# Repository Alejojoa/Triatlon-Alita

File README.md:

# Robot Triatlon - "ALITA" - SPACE ANGELS ROBOTICS

### Robot de competición desarrollado en el año 2024 por "Space Angels Robotics", con el objetivo de participar de los Juegos Bonaerenses del correspondiente año en la categoría de "Triatlón Robótico".
Campéon Regional en la categoría de "Triatlón Robótico" en la Universidad de Quilmes el (22 Ago).
Participación en los Juegos Bonaerenses 2024 (28 Oct. - 2 Nov.)

Llevado a cabo por alumnos de 6to año de la Técnica n°5 "2 de Abril" en la carrera de Electrónica.
Alita es un robot diseñado para fines plenamente educativos, contado con múltiples versiones, con el objetivo de superarse a si misma en cada una de sus etapas.

Todo el proyecto ha sido realizado en Vistual Studio Code con la extensión de PlarformIO en lenguaje C++ Orientado a Objetos.
Diseño de PCBs realizado en KiCad 8.0
Diseño de Hardware3D en Fusion 360

Participantes: Guerra Alejo Joaqín
               Lazzatti Lucas
               Regidor Jeremías
               Romano Iván
               Rossi Mamberti Valentina Jenifer

Director Técnico: Prof. Barzola Maximiliano Andrés

 Este robót cuenta con diferentes categorías, de las cuales cada una tendrá su rama individual con su última versión vigente.

 ## despeja_area
 Rama dedicada a la programación final (Alita V3) en la categoría de "Despeja Area" (Autonomo). Su objetivo será el de quitar de la pista una serie de cubos de la forma más rápida y eficiente posible, sin salir de la pista. 

   -.vscode
        Archivos generados por el IDE Visual Studio Code y la extensión de PlatformIO.
        
   -fimware
        Código actual individual de despeja_area.

 ## sprinter
 Rama dedicada a la programación final (Alita V3) en la categoría de "Velocista" (Autonomo). Su objetivo será el de completar una pista en su totalidad de la forma más rápida posible, pudiendo de igual forma incluir obstáculos o no.

   -.vscode
        Archivos generados por el IDE Visual Studio Code y la extensión de PlatformIO.
        
   -fimware
        Código actual individual de sprinter.

 ## sumo
 Rama dedicada a la programación final (Alita V3) en la categoría de "Sumo RC" (Radio Controlado). Su objertivo será el de quitar del tatami al rival, siendo un operario el encargado de manejar el robot. 

   -.vscode
        Archivos generados por el IDE Visual Studio Code y la extensión de PlatformIO.

   -fimware
        Código actual indiviual de sumo.

 ## menu
 Alita, en todas sus versiónes, incluye un menu comandado por pulsadores incluidos en el lateral izquierdo de robot para mayor comodidad del usuario. En esta rama encontrará la programación dedicada al manejo de esta interfaz. 

  -.vscode
       Archivos generados por el IDE Visual Studio Code y la extensión de PlatformIO.

  -fimware
       Programación de la interfaz de menú.

 ## main
 Esta es la rama principal del repositorio. En ella se encontrará la union de todas las ramas en una sola junto al hardware de Alita.

   -.vscode
        Archivos generados por el IDE Vistual Studio Code y la extensión de PlatformIO.

   -fimware
        Unión de las ramas individuales en una sola para mayor comodidad, dandole así a la interfaz del menu.

   -hardware
        PCBs empleadas en el robot, tanto como principales como drivers y multiplexores.

   -hardware 3D
        Diseños 3D de las diferentes versiones de Alita.

 ## stage
 Rama de pruebas de uniones previas a la rama main.

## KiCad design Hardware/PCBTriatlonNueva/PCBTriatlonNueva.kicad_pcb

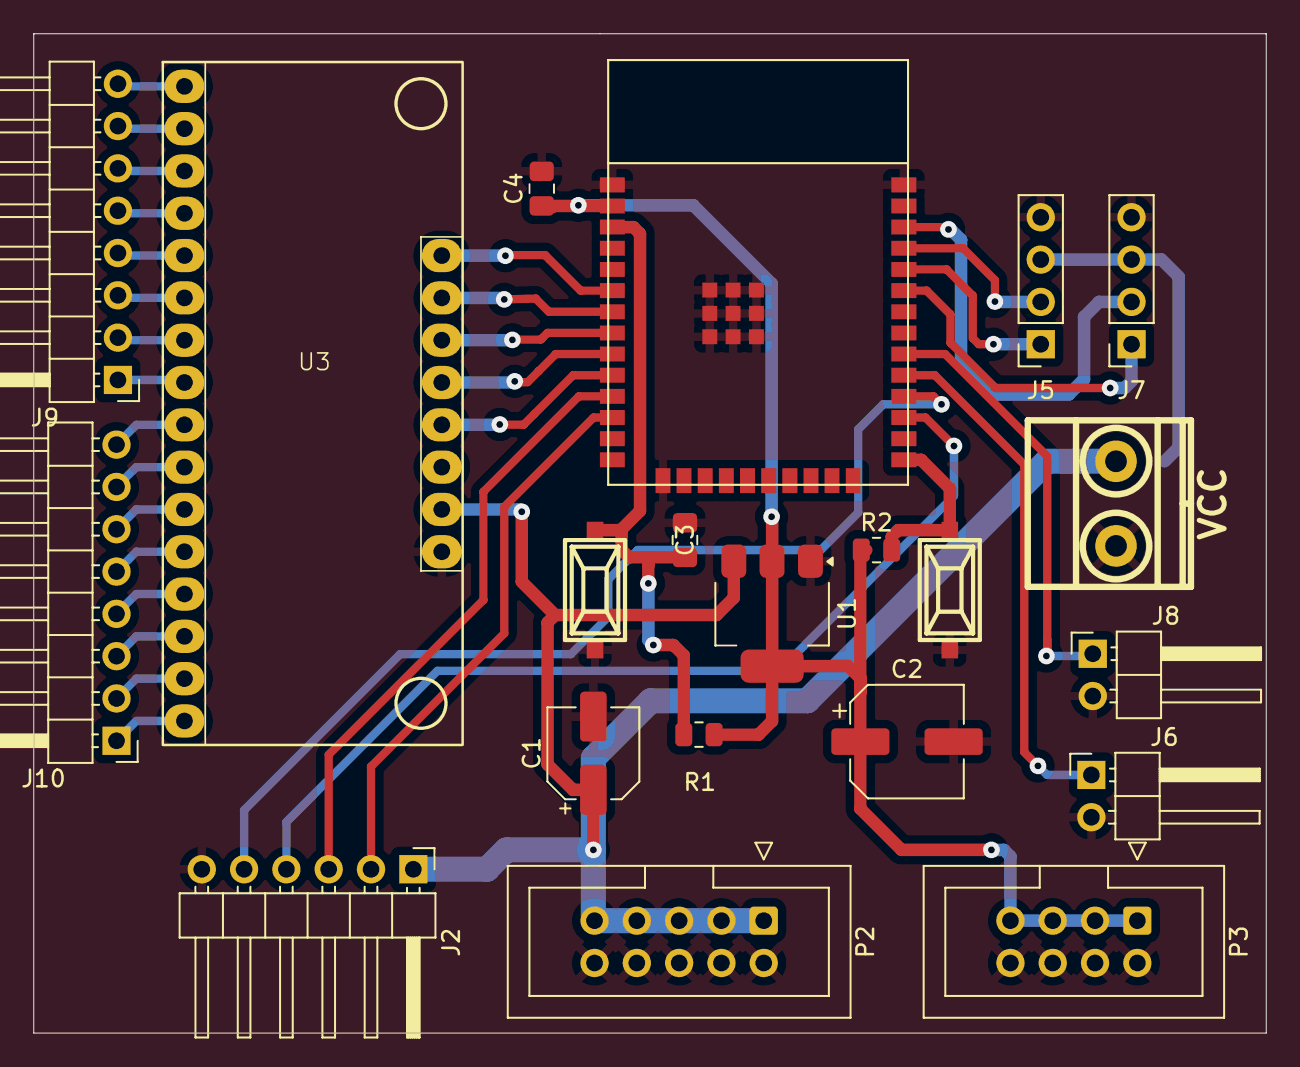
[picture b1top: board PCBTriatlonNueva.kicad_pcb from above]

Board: 2 copper layers, 74.0 x 60.0 mm, 21 parts (0 on the bottom side), 36 nets.

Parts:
C1: 10uF; CP_Elec_5x4.5
C2: 100uF; CP_Elec_6.3x5.9
C3, C4: 100nF; C_0805_2012Metric_Pad1.18x1.45mm_HandSolder
J1: VCC; BORNERA2
J2: Motores; PinHeader_1x06_P2.54mm_Horizontal
J5: Programador; PinSocket_1x04_P2.54mm_Vertical
J6: Boton2; PinHeader_1x02_P2.54mm_Horizontal
J7: I2C; PinSocket_1x04_P2.54mm_Vertical
J8: Boton1; PinHeader_1x02_P2.54mm_Horizontal
J9: MUX_header1; PinHeader_1x08_P2.54mm_Horizontal
J10: MUX_header2; PinHeader_1x08_P2.54mm_Horizontal
P2: 5vMultiplexor; IDC-Header_2x05_P2.54mm_Vertical
P3: 5vMultiplexor; IDC-Header_2x04_P2.54mm_Vertical
R1, R2: 10k; R_0805_2012Metric
SW_BOOT1: SW_Push; Pulsador_SMD_2_ALTO
SW_EN1: SW_Push; Pulsador_SMD_2_ALTO
U1: AMS1117-3.3; SOT-223-3_TabPin2
U2: ESP32-WROOM-32E
U3: MUX 4067; HP4067_module

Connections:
+3V3: C2.1, C4.1, P3.1, P3.3, P3.5, P3.7, R1.1, R2.1, U1.2 (VO), U2.3V3
+5V: C1.1, J1.2, J2.1, J5.3, J7.3, P2.1, P2.3, P2.5, P2.7, P2.9, U1.3 (VI), U3.23 (VCC)
/BOTON1: J6.1, U2.34 (IO5)
/BOTON2: J8.1, U2.35 (IO18)
/EN: C3.1, R1.2, SW_EN1.2, U2.9 (EN)
/IOO: R2.2, SW_BOOT1.2, U2.23 (IO0)
/MA1: J2.3, U2.15 (IO26)
/MA2: J2.2, U2.16 (IO27)
/MB1: J2.4, U2.25 (IO16)
/MB2: J2.5, U2.27 (IO17)
/MULTIPLEXOR1: U2.14 (IO25), U3.21 (S0)
/MULTIPLEXOR2: U2.13 (IO33), U3.20 (S1)
/MULTIPLEXOR3: U2.12 (IO32), U3.19 (S2)
/MULTIPLEXOR4: U2.11 (IO35), U3.18 (S3)
/MULTIPLEXOR5: U2.10 (IO34), U3.17 (SIG)
/RXD: J5.1, U2.40 (RXD0)
/SCL: J7.2, U2.39 (IO22)
/SDA: J7.1, U2.42 (IO21)
/TXD: J5.2, U2.41 (TXD0)
GND: C1.2, C2.2, C3.2, C4.2, J1.1, J2.6, J5.4, J6.2, J7.4, J8.2, P2.2, P2.4, P2.6, P2.8, P2.10, P3.2, P3.4, P3.6, P3.8, SW_BOOT1.1, SW_EN1.1, U1.1 (GND), U2.GND, U3.24 (GND)
unnamed: J9.1, U3.8 (C8)
unnamed: J9.2, U3.7 (C9)
unnamed: J9.3, U3.6 (C10)
unnamed: J9.4, U3.5 (C11)
unnamed: J9.5, U3.4 (C12)
unnamed: J9.6, U3.3 (C13)
unnamed: J9.7, U3.2 (C14)
unnamed: J9.8, U3.1 (C15)
unnamed: J10.1, U3.16 (C0)
unnamed: J10.2, U3.15 (C1)
unnamed: J10.3, U3.14 (C2)
unnamed: J10.4, U3.13 (C3)
unnamed: J10.5, U3.12 (C4)
unnamed: J10.6, U3.11 (C5)
unnamed: J10.7, U3.10 (C6)
unnamed: J10.8, U3.9 (C7)

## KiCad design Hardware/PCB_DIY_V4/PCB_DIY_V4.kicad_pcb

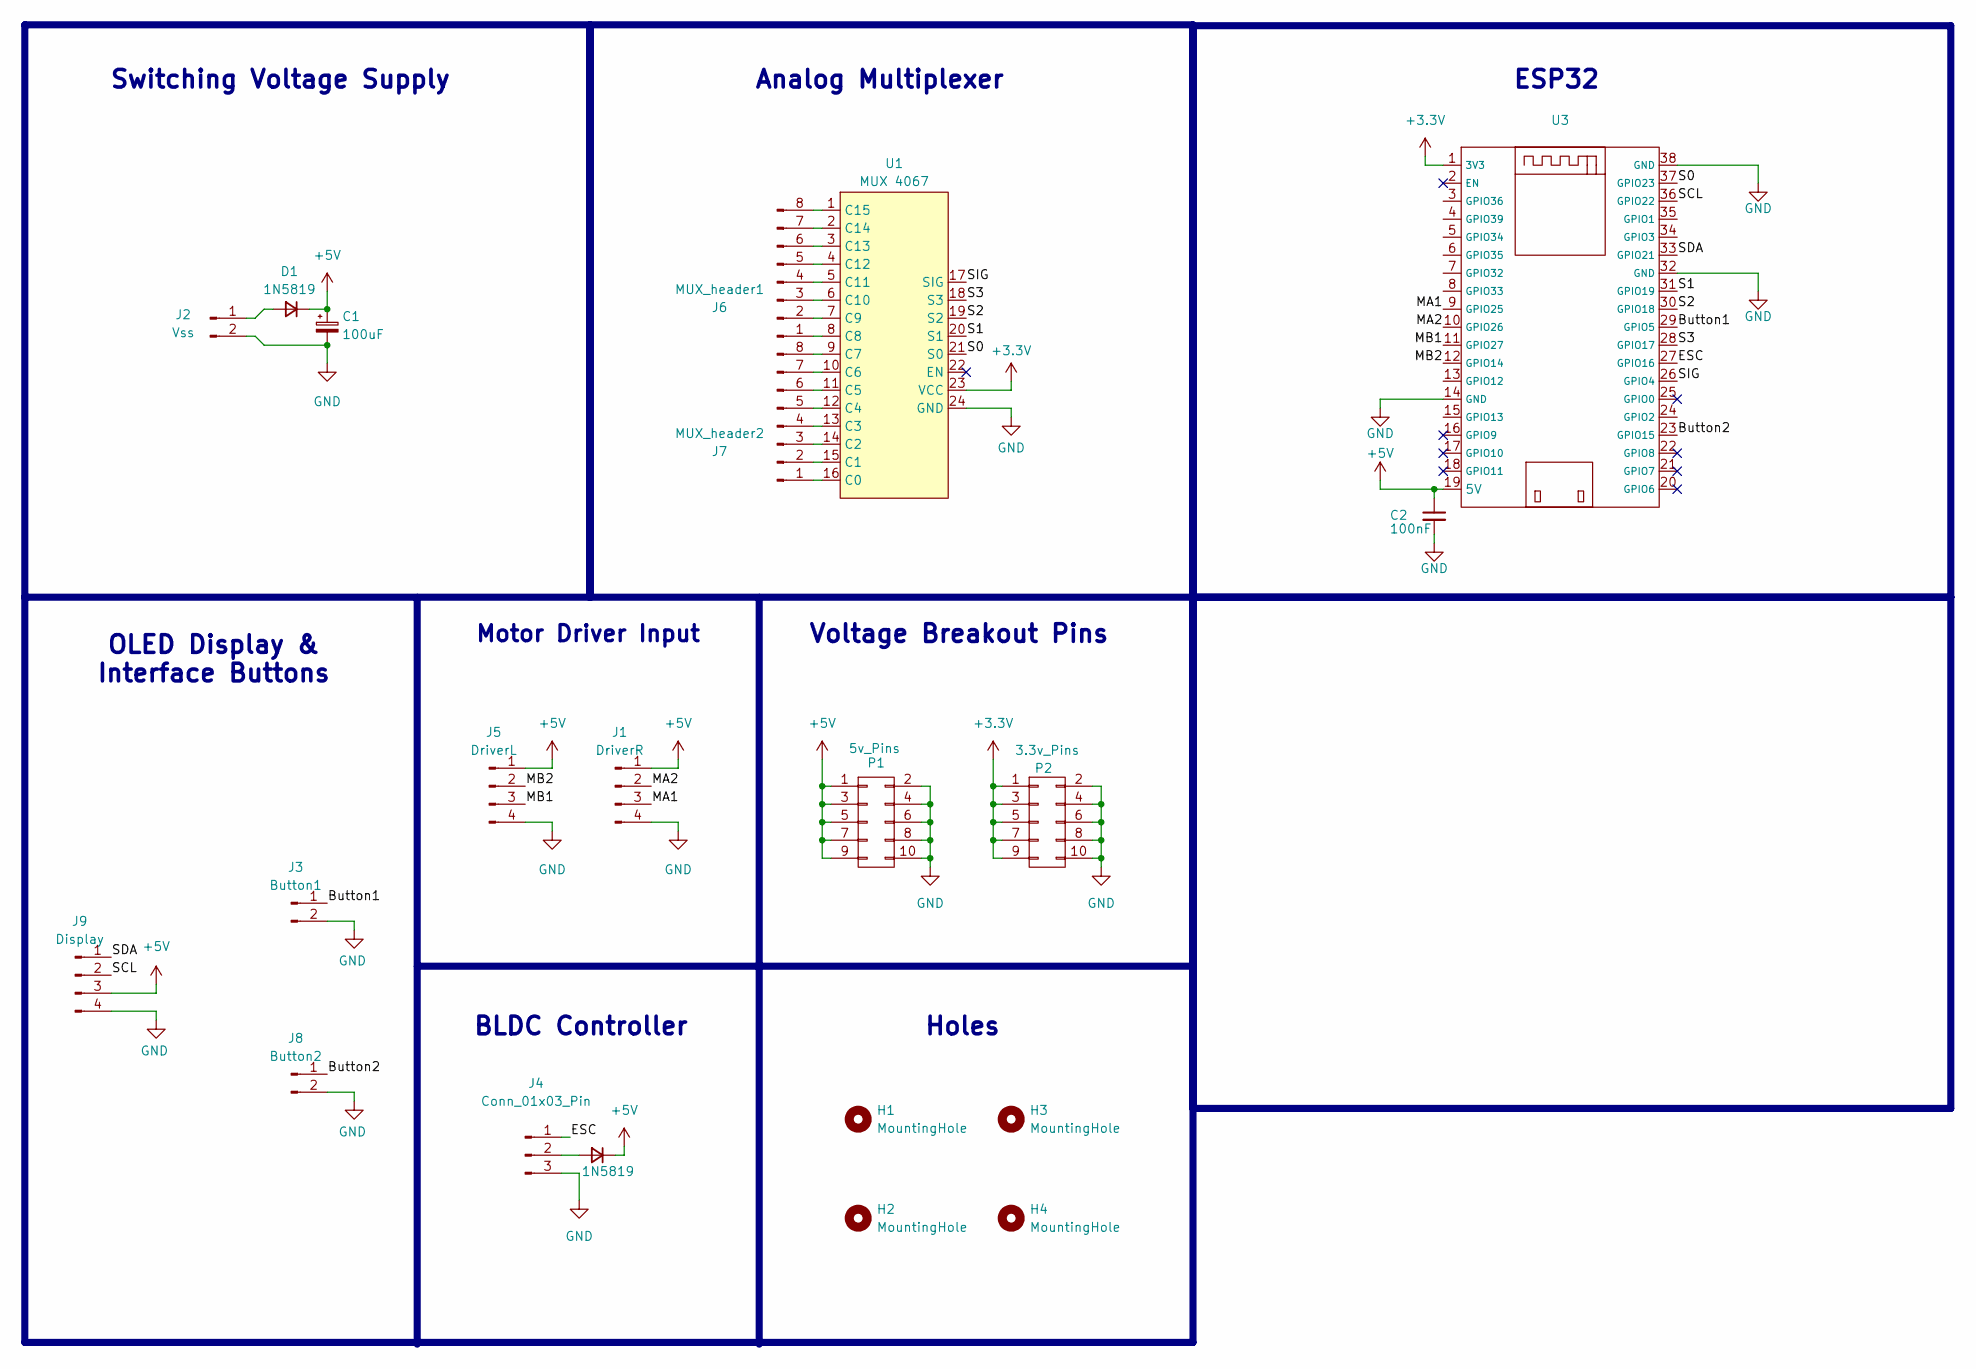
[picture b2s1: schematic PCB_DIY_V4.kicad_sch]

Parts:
C1: 100uF; CP_Elec_5x4.5
C2: 100nF; C_0805_2012Metric_Pad1.18x1.45mm_HandSolder
D1, D2: 1N5819; D_SMA
H1, H2, H3, H4: MountingHole; MountingHole_3.2mm_M3_DIN965
J1: DriverR; PinHeader_1x04_P2.54mm_Horizontal
J2: Vss; PinHeader_1x02_P2.54mm_Horizontal
J3: Button1; PinHeader_1x02_P2.54mm_Horizontal
J4: Conn_01x03_Pin; Molex_KK-254_AE-6410-03A_1x03_P2.54mm_Vertical
J5: DriverL; PinHeader_1x04_P2.54mm_Horizontal
J6: MUX_header1; PinHeader_1x08_P2.54mm_Horizontal
J7: MUX_header2; PinHeader_1x08_P2.54mm_Horizontal
J8: Button2; PinHeader_1x02_P2.54mm_Horizontal
J9: Display; PinHeader_1x04_P2.54mm_Horizontal
P1: 5v_Pins; IDC-Header_2x05_P2.54mm_Vertical
P2: 3.3v_Pins; IDC-Header_2x05_P2.54mm_Vertical
U1: MUX 4067; HP4067_module
U3: Nodemcu_ESP32S_38pin

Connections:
+3.3V: P2.1, P2.3, P2.5, P2.7, P2.9, U1.23 (VCC), U3.1 (3V3)
+5V: C1.1, C2.1, D1.1 (K), D2.1 (K), J1.1, J5.1, J9.3, P1.1, P1.3, P1.5, P1.7, P1.9, U3.19 (5V)
/Button1: J3.1, U3.29 (GPIO5)
/Button2: J8.1, U3.23 (GPIO15)
/ESC: J4.1, U3.27 (GPIO16)
/MA1: J1.3, U3.9 (GPIO25)
/MA2: J1.2, U3.10 (GPIO26)
/MB1: J5.3, U3.11 (GPIO27)
/MB2: J5.2, U3.12 (GPIO14)
/S0: U1.21 (S0), U3.37 (GPIO23)
/S1: U1.20 (S1), U3.31 (GPIO19)
/S2: U1.19 (S2), U3.30 (GPIO18)
/S3: U1.18 (S3), U3.28 (GPIO17)
/SCL: J9.2, U3.36 (GPIO22)
/SDA: J9.1, U3.33 (GPIO21)
/SIG: U1.17 (SIG), U3.26 (GPIO4)
GND: C1.2, C2.2, J1.4, J2.2, J3.2, J4.3, J5.4, J8.2, J9.4, P1.2, P1.4, P1.6, P1.8, P1.10, P2.2, P2.4, P2.6, P2.8, P2.10, U1.24 (GND), U3.14 (GND), U3.32 (GND), U3.38 (GND)
unnamed: D1.2 (A), J2.1
unnamed: D2.2 (A), J4.2
unnamed: J6.1, U1.8 (C8)
unnamed: J6.2, U1.7 (C9)
unnamed: J6.3, U1.6 (C10)
unnamed: J6.4, U1.5 (C11)
unnamed: J6.5, U1.4 (C12)
unnamed: J6.6, U1.3 (C13)
unnamed: J6.7, U1.2 (C14)
unnamed: J6.8, U1.1 (C15)
unnamed: J7.1, U1.16 (C0)
unnamed: J7.2, U1.15 (C1)
unnamed: J7.3, U1.14 (C2)
unnamed: J7.4, U1.13 (C3)
unnamed: J7.5, U1.12 (C4)
unnamed: J7.6, U1.11 (C5)
unnamed: J7.7, U1.10 (C6)
unnamed: J7.8, U1.9 (C7)

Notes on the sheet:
Analog Multiplexer
Switching Voltage Supply
Holes
BLDC Controller
Voltage Breakout Pins
OLED Display & Interface Buttons
Motor Driver Input
ESP32

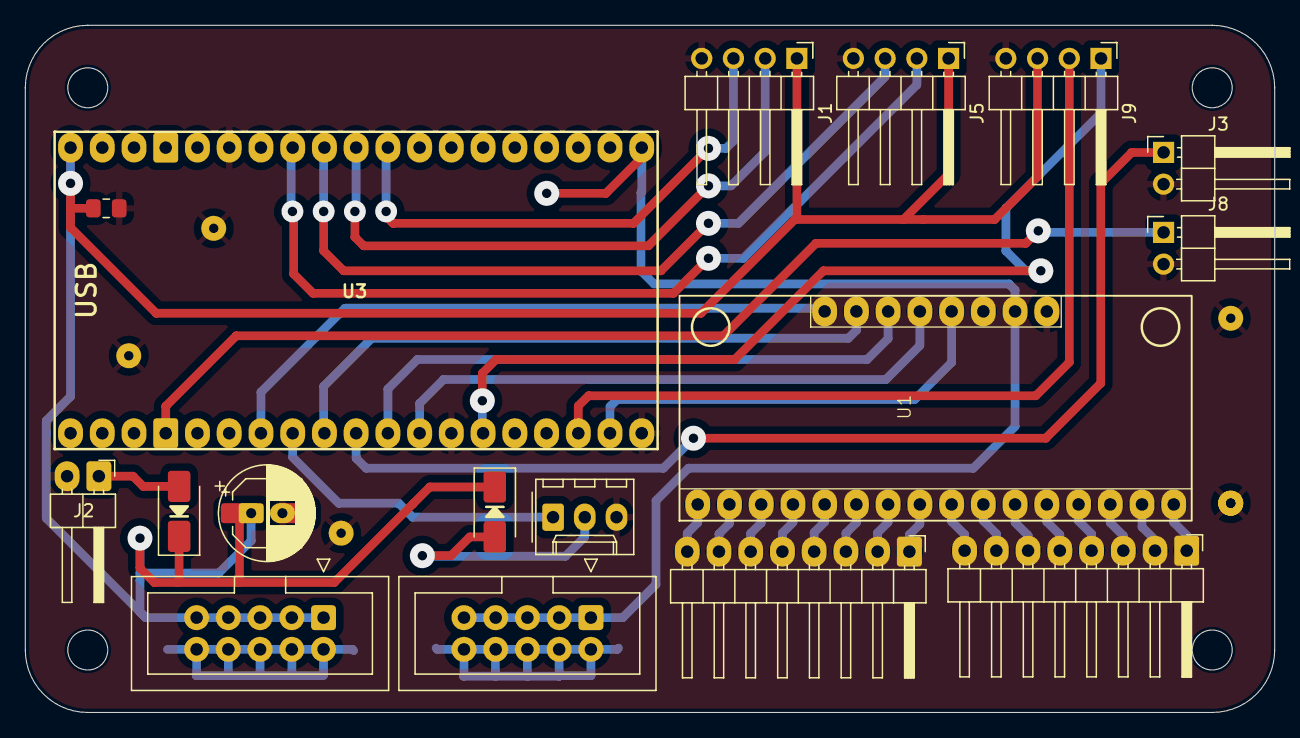
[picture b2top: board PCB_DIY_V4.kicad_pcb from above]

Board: 2 copper layers, 100.0 x 55.0 mm, 21 parts (0 on the bottom side), 35 nets.

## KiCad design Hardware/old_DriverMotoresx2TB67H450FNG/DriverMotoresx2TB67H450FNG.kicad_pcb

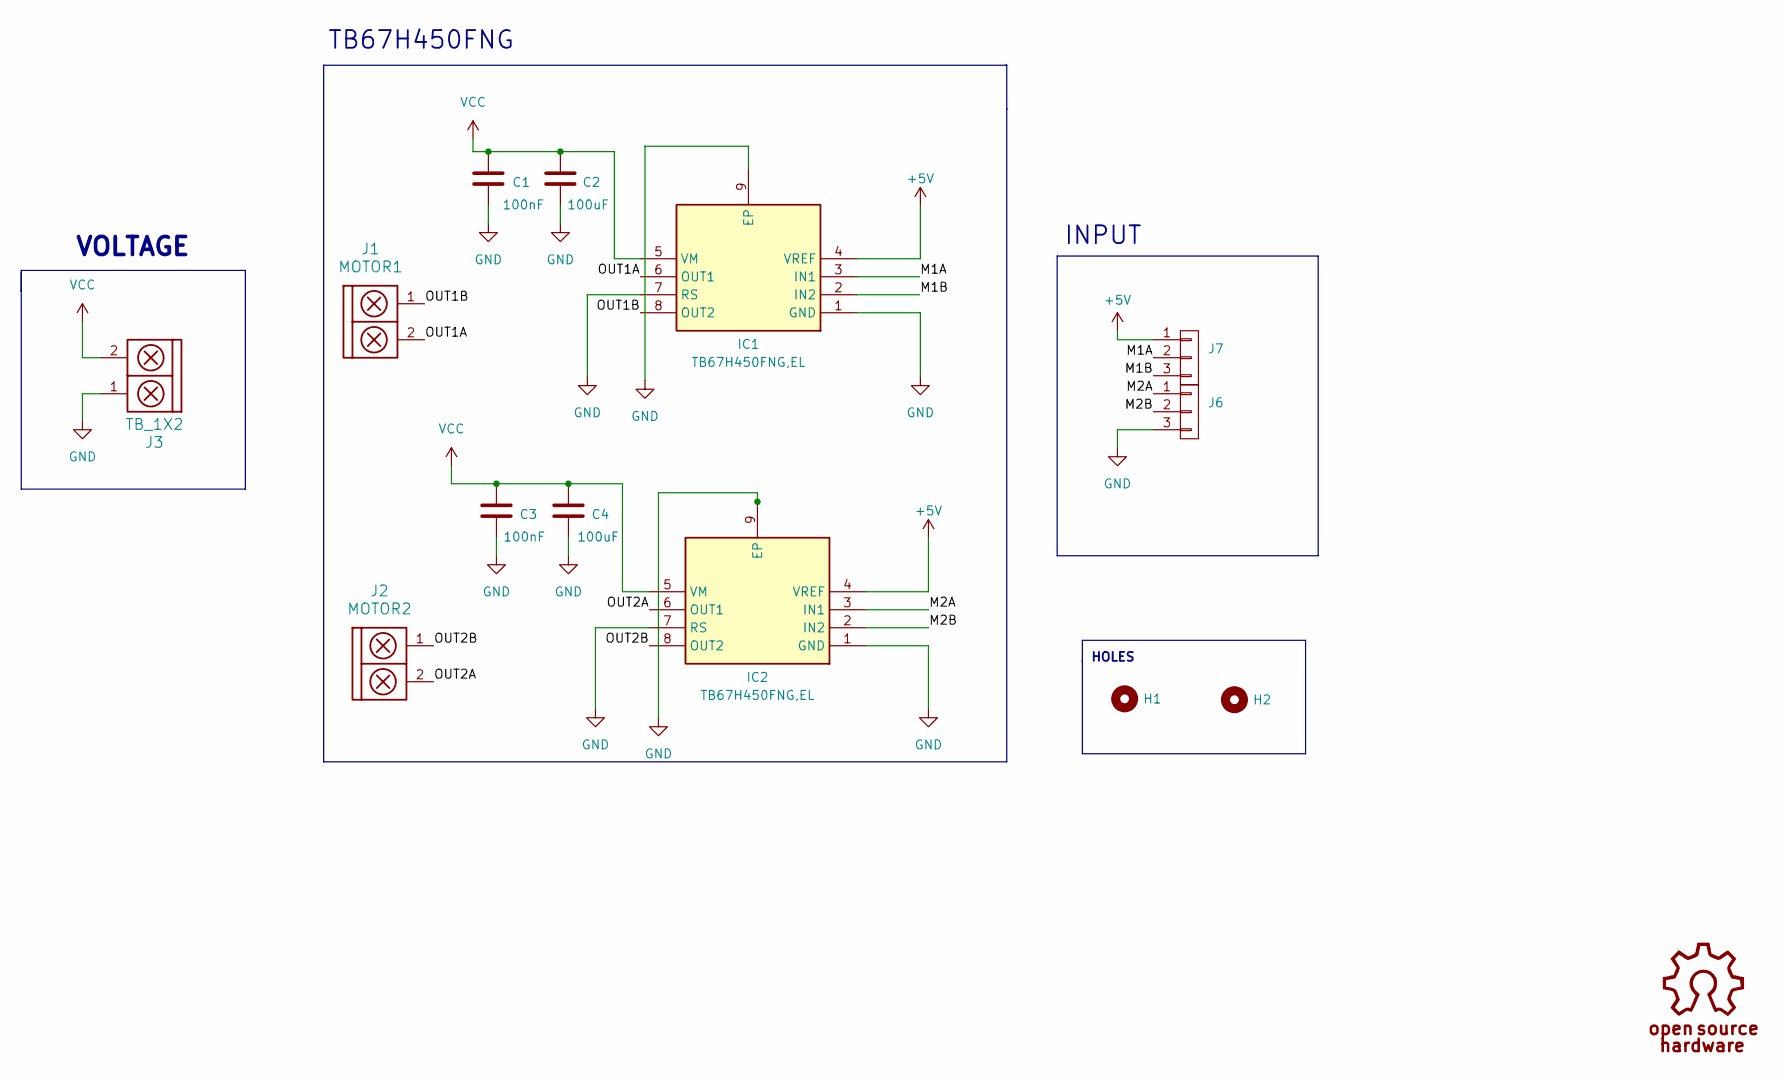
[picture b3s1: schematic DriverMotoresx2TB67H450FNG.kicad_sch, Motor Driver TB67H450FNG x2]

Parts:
C1, C3: 100nF; C_0805_2012Metric_Pad1.18x1.45mm_HandSolder
C2, C4: 100uF; CP_Radial_D10.0mm_P5.00mm
H1, H2: Mounting_Hole; hole_3mm
IC1, IC2: TB67H450FNG,EL; SOIC127P600X170-9N; Mouser Part Number 757-TB67H450FNGEL
J1: MOTOR1; BORNERA2_AZUL
J2: MOTOR2; BORNERA2_AZUL
J3: TB_1X2; BORNERA2_AZUL
J6, J7: Conn_01X03; PinHeader_1x03_P2.54mm_Vertical

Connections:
+5V: IC1.4 (VREF), IC2.4 (VREF), J7.1
/M1A: IC1.3 (IN1), J7.2
/M1B: IC1.2 (IN2), J7.3
/M2A: IC2.3 (IN1), J6.1
/M2B: IC2.2 (IN2), J6.2
/OUT1A: IC1.6 (OUT1), J1.2
/OUT1B: IC1.8 (OUT2), J1.1
/OUT2A: IC2.6 (OUT1), J2.2
/OUT2B: IC2.8 (OUT2), J2.1
GND: C1.2, C2.2, C3.2, C4.2, IC1.1 (GND), IC1.7 (RS), IC1.9 (EP), IC2.1 (GND), IC2.7 (RS), IC2.9 (EP), J3.1, J6.3
VCC: C1.1, C2.1, C3.1, C4.1, IC1.5 (VM), IC2.5 (VM), J3.2

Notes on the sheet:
HOLES
INPUT
TB67H450FNG
VOLTAGE

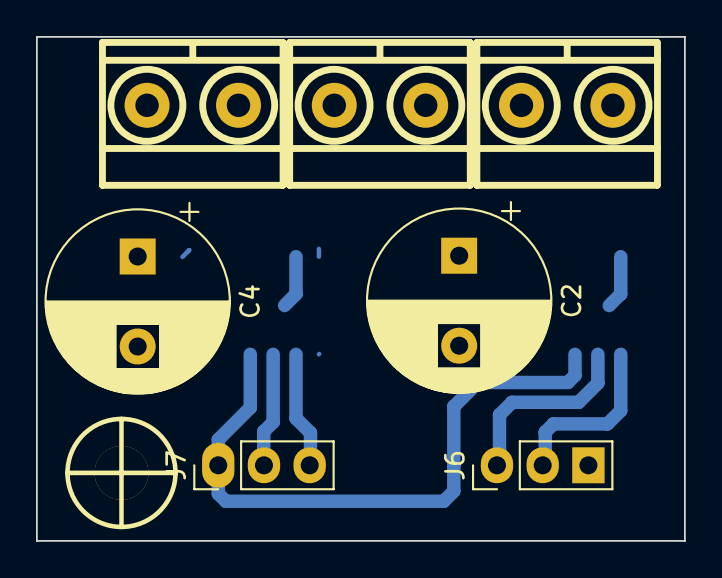
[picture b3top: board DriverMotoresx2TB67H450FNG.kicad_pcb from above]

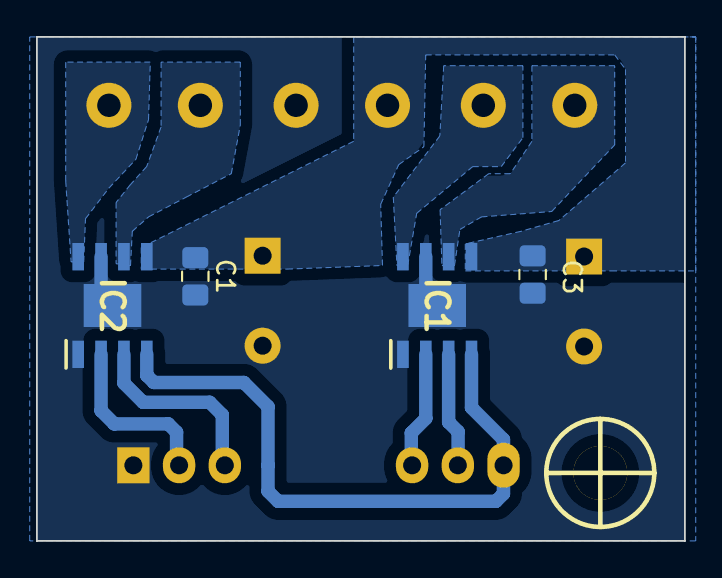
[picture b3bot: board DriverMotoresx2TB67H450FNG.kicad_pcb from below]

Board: 2 copper layers, 36.0 x 28.0 mm, 12 parts (4 on the bottom side), 11 nets.

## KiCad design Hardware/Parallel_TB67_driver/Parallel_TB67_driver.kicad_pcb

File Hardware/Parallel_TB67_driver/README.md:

# Parallel_TB67_driver
tiny repositorie for tiny pcb

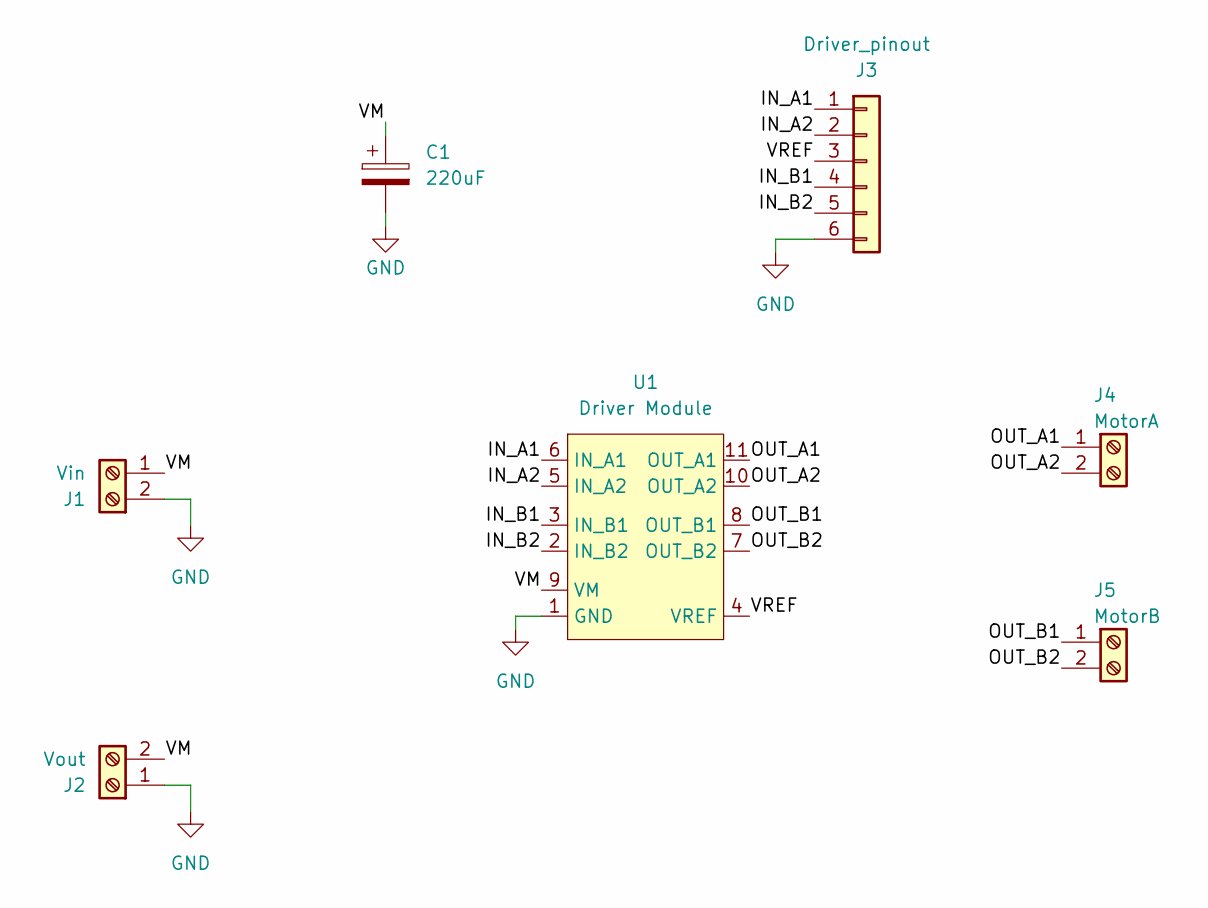
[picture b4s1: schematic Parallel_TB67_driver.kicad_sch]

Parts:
C1: 220uF; CP_Radial_D10.0mm_P3.50mm
J1: Vin; BORNERA2_AZUL
J2: Vout; BORNERA2_AZUL
J3: Driver_pinout; Molex_KK-254_AE-6410-06A_1x06_P2.54mm_Vertical
J4: MotorA; BORNERA2_AZUL
J5: MotorB; BORNERA2_AZUL
U1: Driver Module; Dual-Driver-Module

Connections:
/IN_A1: J3.1, U1.6 (IN_A1)
/IN_A2: J3.2, U1.5 (IN_A2)
/IN_B1: J3.4, U1.3 (IN_B1)
/IN_B2: J3.5, U1.2 (IN_B2)
/OUT_A1: J4.1, U1.11 (OUT_A1)
/OUT_A2: J4.2, U1.10 (OUT_A2)
/OUT_B1: J5.1, U1.8 (OUT_B1)
/OUT_B2: J5.2, U1.7 (OUT_B2)
/VM: C1.1, J1.1 (Pin_2), J2.2, U1.9 (VM)
/VREF: J3.3, U1.4 (VREF)
GND: C1.2, J1.2 (Pin_1), J2.1, J3.6, U1.1 (GND)

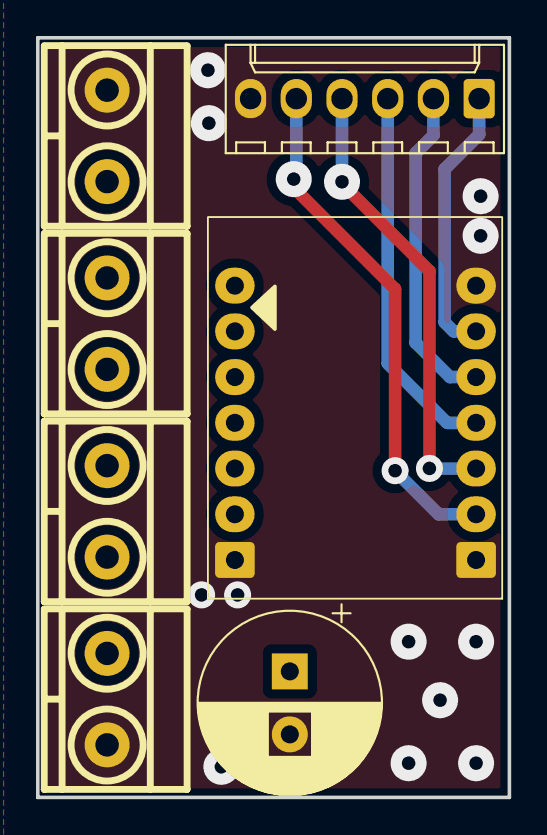
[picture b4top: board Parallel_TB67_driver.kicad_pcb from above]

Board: 2 copper layers, 26.2 x 42.2 mm, 7 parts (0 on the bottom side), 11 nets.

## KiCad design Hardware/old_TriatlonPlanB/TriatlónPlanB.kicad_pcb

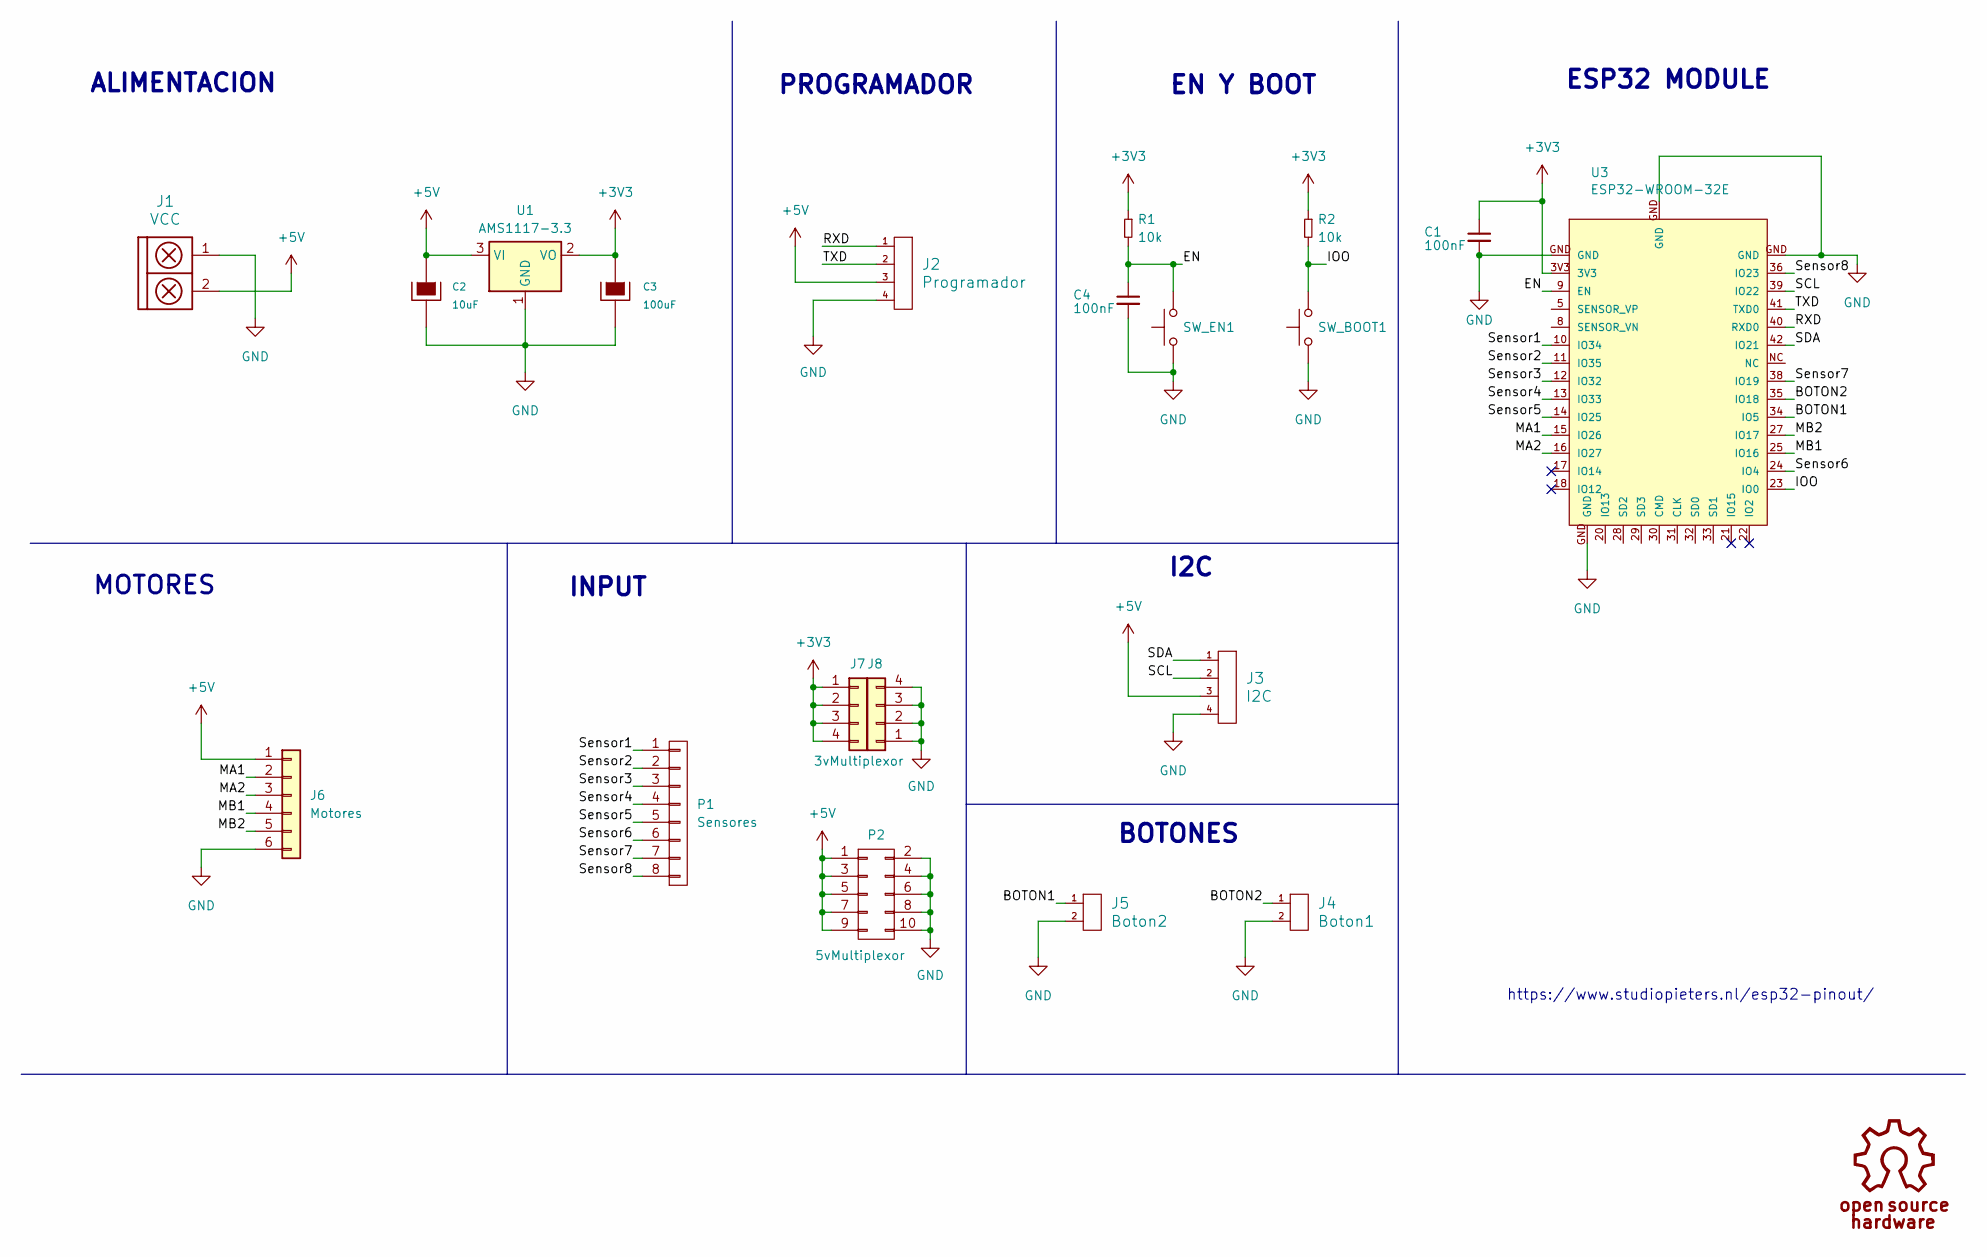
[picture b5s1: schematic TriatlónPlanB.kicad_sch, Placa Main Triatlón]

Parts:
C1, C4: 100nF; C_0805
C2: 10uF; CP_Elec_5x4.5
C3: 100uF; CP_Elec_6.3x5.9
J1: VCC; BORNERA2_AZUL
J2: Programador; PinSocket_1x04_P2.54mm_Vertical
J3: I2C; PinSocket_1x04_P2.54mm_Vertical
J4: Boton1; PinHeader_1x02_P2.54mm_Vertical
J5: Boton2; PinHeader_1x02_P2.54mm_Vertical
J6: Motores; Pin_Header_6
J7, J8: 3vMultiplexor; pin_strip_4
P1: Sensores; PinSocket_1x08_P2.54mm_Vertical
P2: 5vMultiplexor; Pin_Header_02x05
R1, R2: 10k; R_0805_2012Metric
SW_BOOT1: SW_Push; Pulsador_SMD_2_ALTO
SW_EN1: SW_Push; Pulsador_SMD_2_ALTO
U1: AMS1117-3.3; SOT-223-3_TabPin2
U3: ESP32-WROOM-32E

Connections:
+3V3: C1.1, C3.1, J7.1, J7.2, J7.3, J7.4, R1.1, R2.1, U1.2 (VO), U3.3V3
+5V: C2.1, J1.2, J2.3, J3.3, J6.1, P2.1, P2.3, P2.5, P2.7, P2.9, U1.3 (VI)
/BOTON1: J5.1, U3.34 (IO5)
/BOTON2: J4.1, U3.35 (IO18)
/EN: C4.1, R1.2, SW_EN1.2, U3.9 (EN)
/IOO: R2.2, SW_BOOT1.2, U3.23 (IO0)
/MA1: J6.2, U3.15 (IO26)
/MA2: J6.3, U3.16 (IO27)
/MB1: J6.4, U3.25 (IO16)
/MB2: J6.5, U3.27 (IO17)
/RXD: J2.1, U3.40 (RXD0)
/SCL: J3.2, U3.39 (IO22)
/SDA: J3.1, U3.42 (IO21)
/Sensor1: P1.1, U3.10 (IO34)
/Sensor2: P1.2, U3.11 (IO35)
/Sensor3: P1.3, U3.12 (IO32)
/Sensor4: P1.4, U3.13 (IO33)
/Sensor5: P1.5, U3.14 (IO25)
/Sensor7: P1.7, U3.38 (IO19)
/Sensor8: P1.8, U3.36 (IO23)
/TXD: J2.2, U3.41 (TXD0)
GND: C1.2, C2.2, C3.2, C4.2, J1.1, J2.4, J3.4, J4.2, J5.2, J6.6, J8.1, J8.2, J8.3, J8.4, P2.2, P2.4, P2.6, P2.8, P2.10, SW_BOOT1.1, SW_EN1.1, U1.1 (GND), U3.GND

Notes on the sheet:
INPUT
BOTONES
ALIMENTACION
I2C
EN Y BOOT
ESP32 MODULE
PROGRAMADOR
https://www.studiopieters.nl/esp32-pinout/
MOTORES

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
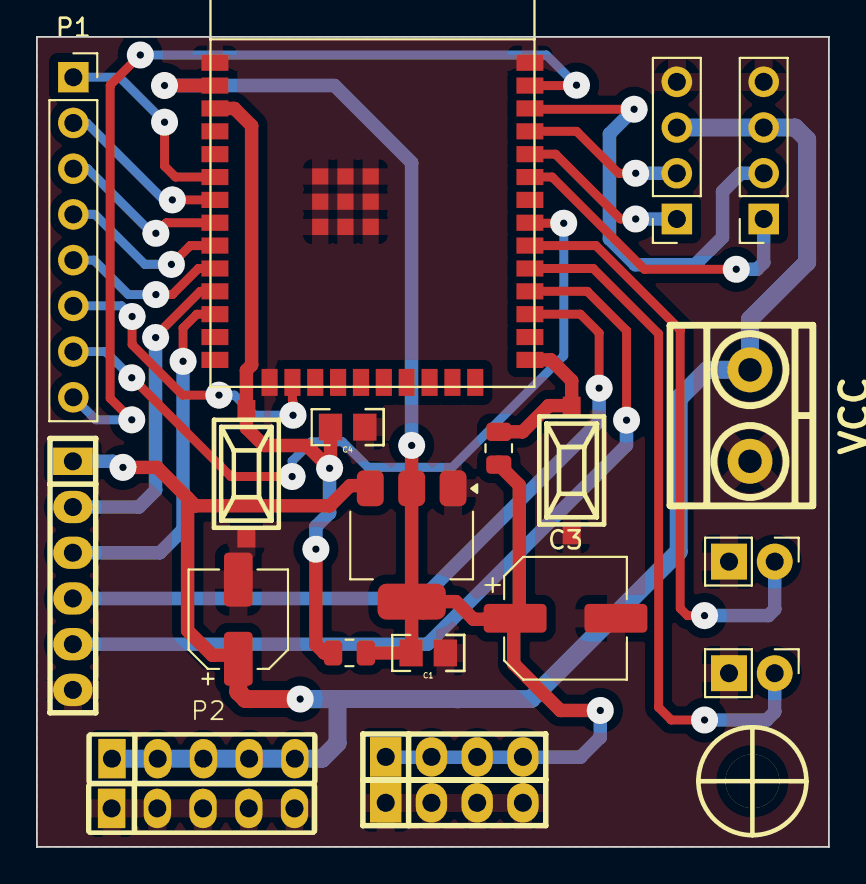
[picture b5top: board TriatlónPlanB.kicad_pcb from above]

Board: 2 copper layers, 44.0 x 45.0 mm, 21 parts (0 on the bottom side), 23 nets.

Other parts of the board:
hole_3mm: VAL**; hole_3mm

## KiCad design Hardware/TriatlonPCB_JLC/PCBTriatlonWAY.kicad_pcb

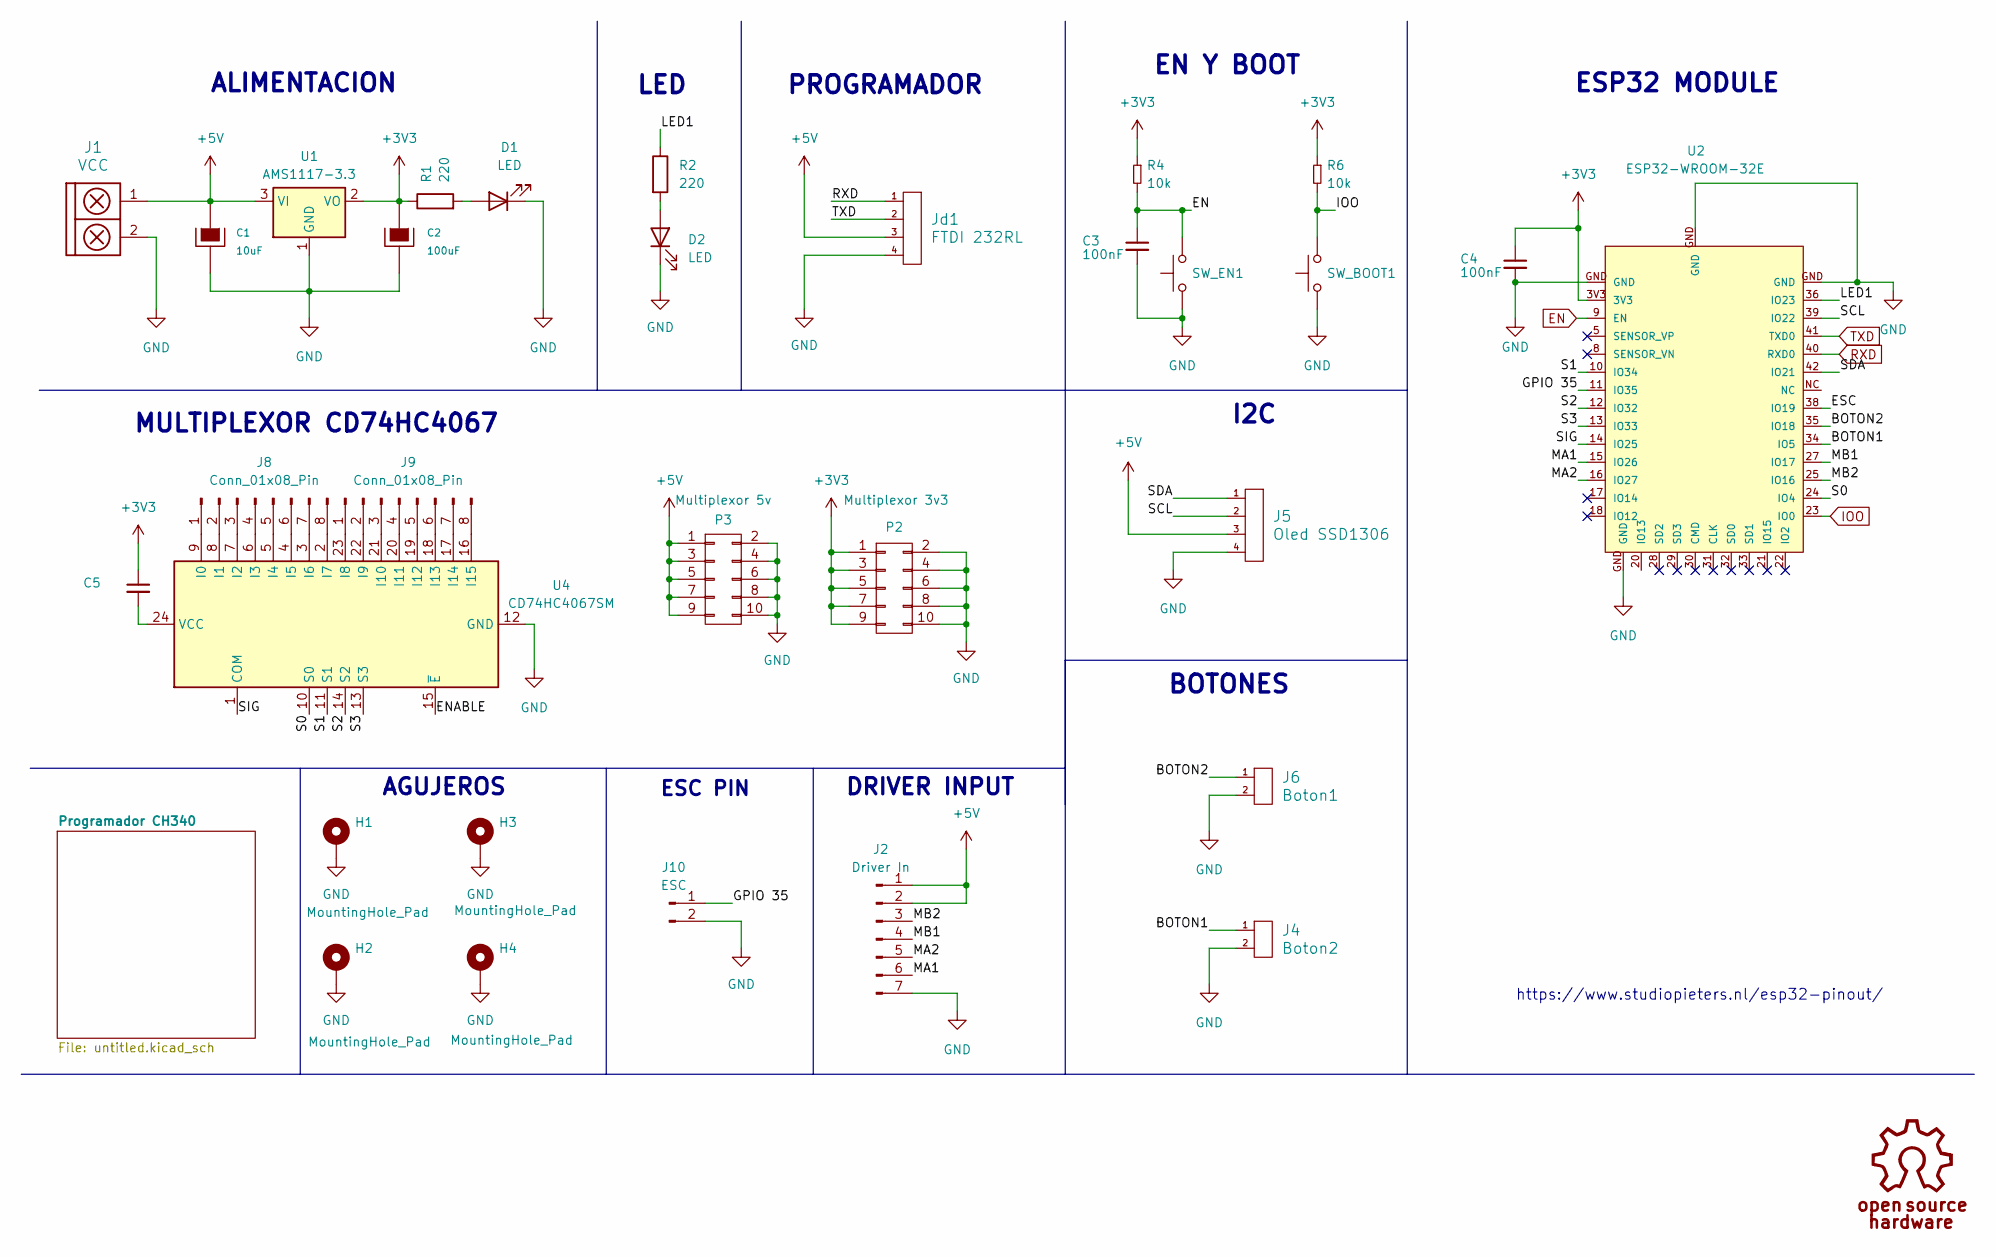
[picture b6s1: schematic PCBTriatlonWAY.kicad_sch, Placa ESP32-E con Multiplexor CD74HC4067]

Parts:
C1: 10uF; CP_Elec_5x4.5
C2: 100uF; CP_Elec_6.3x5.9
C3, C4: 100nF; C_0805_2012Metric_Pad1.18x1.45mm_HandSolder
C5: C_0805_2012Metric_Pad1.18x1.45mm_HandSolder
D1, D2: LED; LED_0805_2012Metric_Pad1.15x1.40mm_HandSolder
H1, H2, H3, H4: MountingHole_Pad; MountingHole_3mm_Pad_Via
J1: VCC; BORNERA2_DUO
J2: Driver In; PinHeader_1x07_P2.54mm_Horizontal
J4: Boton2; PinHeader_1x02_P2.54mm_Horizontal
J5: Oled SSD1306; Molex_KK-254_AE-6410-04A_1x04_P2.54mm_Vertical
J6: Boton1; PinHeader_1x02_P2.54mm_Horizontal
J8, J9: Conn_01x08_Pin; PinHeader_1x08_P2.54mm_Horizontal
J10: ESC; Molex_KK-254_AE-6410-02A_1x02_P2.54mm_Vertical
Jd1: FTDI 232RL; PinHeader_1x04_P2.54mm_Vertical
P2: Multiplexor 3v3; IDC-Header_2x05_P2.54mm_Vertical
P3: Multiplexor 5v; IDC-Header_2x05_P2.54mm_Vertical
R1, R2: 220; R_0805_2012Metric_Pad1.20x1.40mm_HandSolder
R4, R6: 10k; R_0805_2012Metric_Pad1.20x1.40mm_HandSolder
SW_BOOT1: SW_Push; Pulsador_SMD_2_BAJO
SW_EN1: SW_Push; Pulsador_SMD_2_BAJO
U1: AMS1117-3.3; SOT-223-3_TabPin2
U2: ESP32-WROOM-32E
U4: CD74HC4067SM; SSOP-24_5.3x8.2mm_P0.65mm

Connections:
+3V3: C2.1, C4.1, C5.1, P2.1, P2.3, P2.5, P2.7, P2.9, R1.1, R4.1, R6.1, U1.2 (VO), U2.3V3
+5V: C1.1, J1.1, J2.1, J2.2, J5.3, Jd1.3, P3.1, P3.3, P3.5, P3.7, P3.9, U1.3 (VI); also elsewhere on the board
/BOTON1: J4.1, U2.34 (IO5)
/BOTON2: J6.1, U2.35 (IO18)
/ENABLE: U4.15 (~E)
/ESC: U2.38 (IO19)
/GPIO 35: J10.1, U2.11 (IO35)
/LED1: R2.1, U2.36 (IO23)
/MA1: J2.6, U2.15 (IO26)
/MA2: J2.5, U2.16 (IO27)
/MB1: J2.4, U2.27 (IO17)
/MB2: J2.3, U2.25 (IO16)
/S0: U2.24 (IO4), U4.10 (S0)
/S1: U2.10 (IO34), U4.11 (S1)
/S2: U2.12 (IO32), U4.14 (S2)
/S3: U2.13 (IO33), U4.13 (S3)
/SCL: J5.2, U2.39 (IO22)
/SDA: J5.1, U2.42 (IO21)
/SIG: U2.14 (IO25), U4.1 (COM)
EN: C3.1, R4.2, SW_EN1.2, U2.9 (EN)
GND: C1.2, C2.2, C3.2, C4.2, D1.1 (K), D2.1 (K), H1.1, H2.1, H3.1, H4.1, J1.2, J2.7, J4.2, J5.4, J6.2, J10.2, Jd1.4, P2.2, P2.4, P2.6, P2.8, P2.10, P3.2, P3.4, P3.6, P3.8, P3.10, SW_BOOT1.1, SW_EN1.1, U1.1 (GND), U2.GND, U4.12 (GND); also elsewhere on the board
IOO: R6.2, SW_BOOT1.2, U2.23 (IO0)
unnamed: D1.2 (A), R1.2
unnamed: D2.2 (A), R2.2
unnamed: J8.1, U4.9 (I0)
unnamed: J8.2, U4.8 (I1)
unnamed: J8.3, U4.7 (I2)
unnamed: J8.4, U4.6 (I3)
unnamed: J8.5, U4.5 (I4)
unnamed: J8.6, U4.4 (I5)
unnamed: J8.7, U4.3 (I6)
unnamed: J8.8, U4.2 (I7)
unnamed: J9.1, U4.23 (I8)
unnamed: J9.2, U4.22 (I9)
unnamed: J9.3, U4.21 (I10)
unnamed: J9.4, U4.20 (I11)
unnamed: J9.5, U4.19 (I12)
unnamed: J9.6, U4.18 (I13)
unnamed: J9.7, U4.17 (I14)
unnamed: J9.8, U4.16 (I15)
unnamed: C5.2, U4.24 (VCC)
RXD: Jd1.1, U2.40 (RXD0); also elsewhere on the board
TXD: Jd1.2, U2.41 (TXD0); also elsewhere on the board

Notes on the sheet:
ALIMENTACION
DRIVER INPUT
ESC PIN
BOTONES
https://www.studiopieters.nl/esp32-pinout/
MULTIPLEXOR CD74HC4067
EN Y BOOT
AGUJEROS
LED
ESP32 MODULE
I2C
PROGRAMADOR
